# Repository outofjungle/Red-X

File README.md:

# Red-X

Proof of concept 3D PCB design

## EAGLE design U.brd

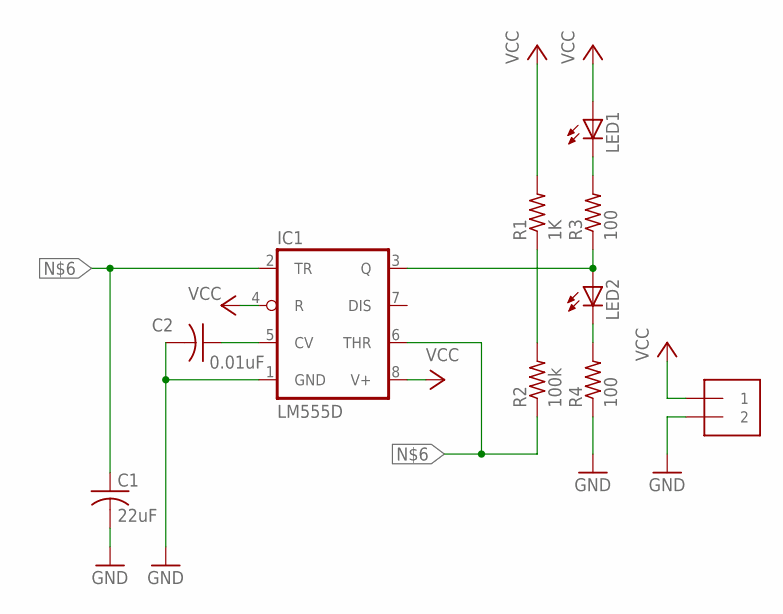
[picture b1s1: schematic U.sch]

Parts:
C1: 22uF; C0805
C2: 0.01uF; C0805
IC1: LM555D; SO08
J1: 1X2-3.5MM
LED1, LED2: LEDCHIPLED_0805; CHIPLED_0805
R1: 1K; R0805
R2: 100k; R0805
R3, R4: 100; R0805

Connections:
GND: C1.2, C2.2, IC1.1 (GND), J1.2, R4.1
unnamed: LED1.C, R3.2
unnamed: IC1.3 (Q), LED2.A, R3.1
unnamed: LED2.C, R4.2
unnamed: R1.1, R2.2
unnamed: C1.1, IC1.2 (TR), IC1.6 (THR), R2.1
unnamed: C2.1, IC1.5 (CV)
VCC: IC1.4 (R), IC1.8 (V+), J1.1, LED1.A, R1.2

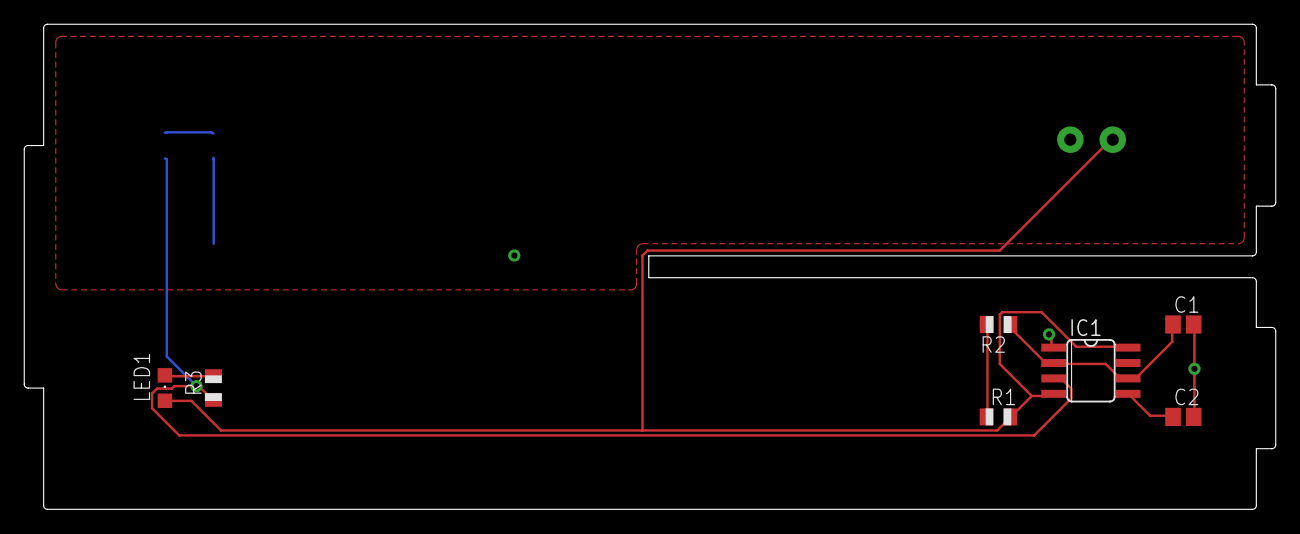
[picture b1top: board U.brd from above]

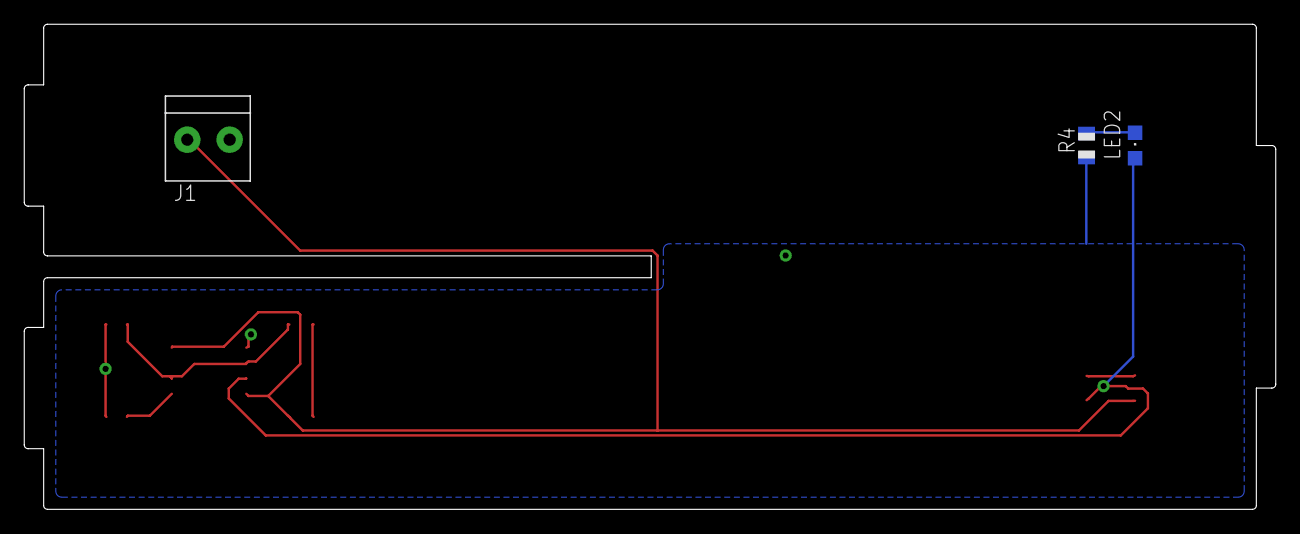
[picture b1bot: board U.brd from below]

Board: 2 copper layers, 103.2 x 40.0 mm, 10 parts (3 on the bottom side), 8 nets.

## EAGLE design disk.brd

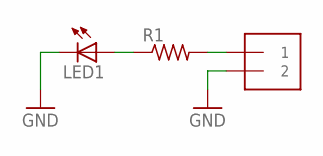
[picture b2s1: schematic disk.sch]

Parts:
J1: 1X2-3.5MM
LED1: LEDCHIPLED_0805; CHIPLED_0805
R1: R-US_M0805; M0805

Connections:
GND: J1.2, LED1.C
unnamed: J1.1, R1.2
unnamed: LED1.A, R1.1

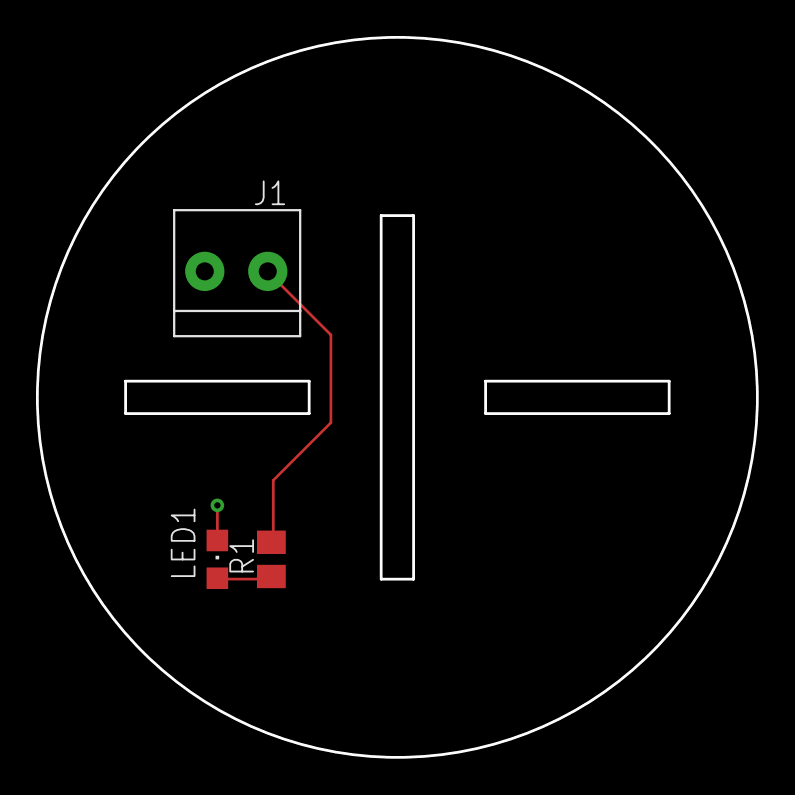
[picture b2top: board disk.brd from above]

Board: 2 copper layers, 40.0 x 40.0 mm, 3 parts (0 on the bottom side), 3 nets.

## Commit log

2021-04-09 Mostly done U board with blinky curcuit
2021-04-09 eagle updated the file
2021-04-09 end cap disk brd
2021-04-09 renamed circuits and fixed all dimensions
2021-04-13 reworked boards and gerber files
